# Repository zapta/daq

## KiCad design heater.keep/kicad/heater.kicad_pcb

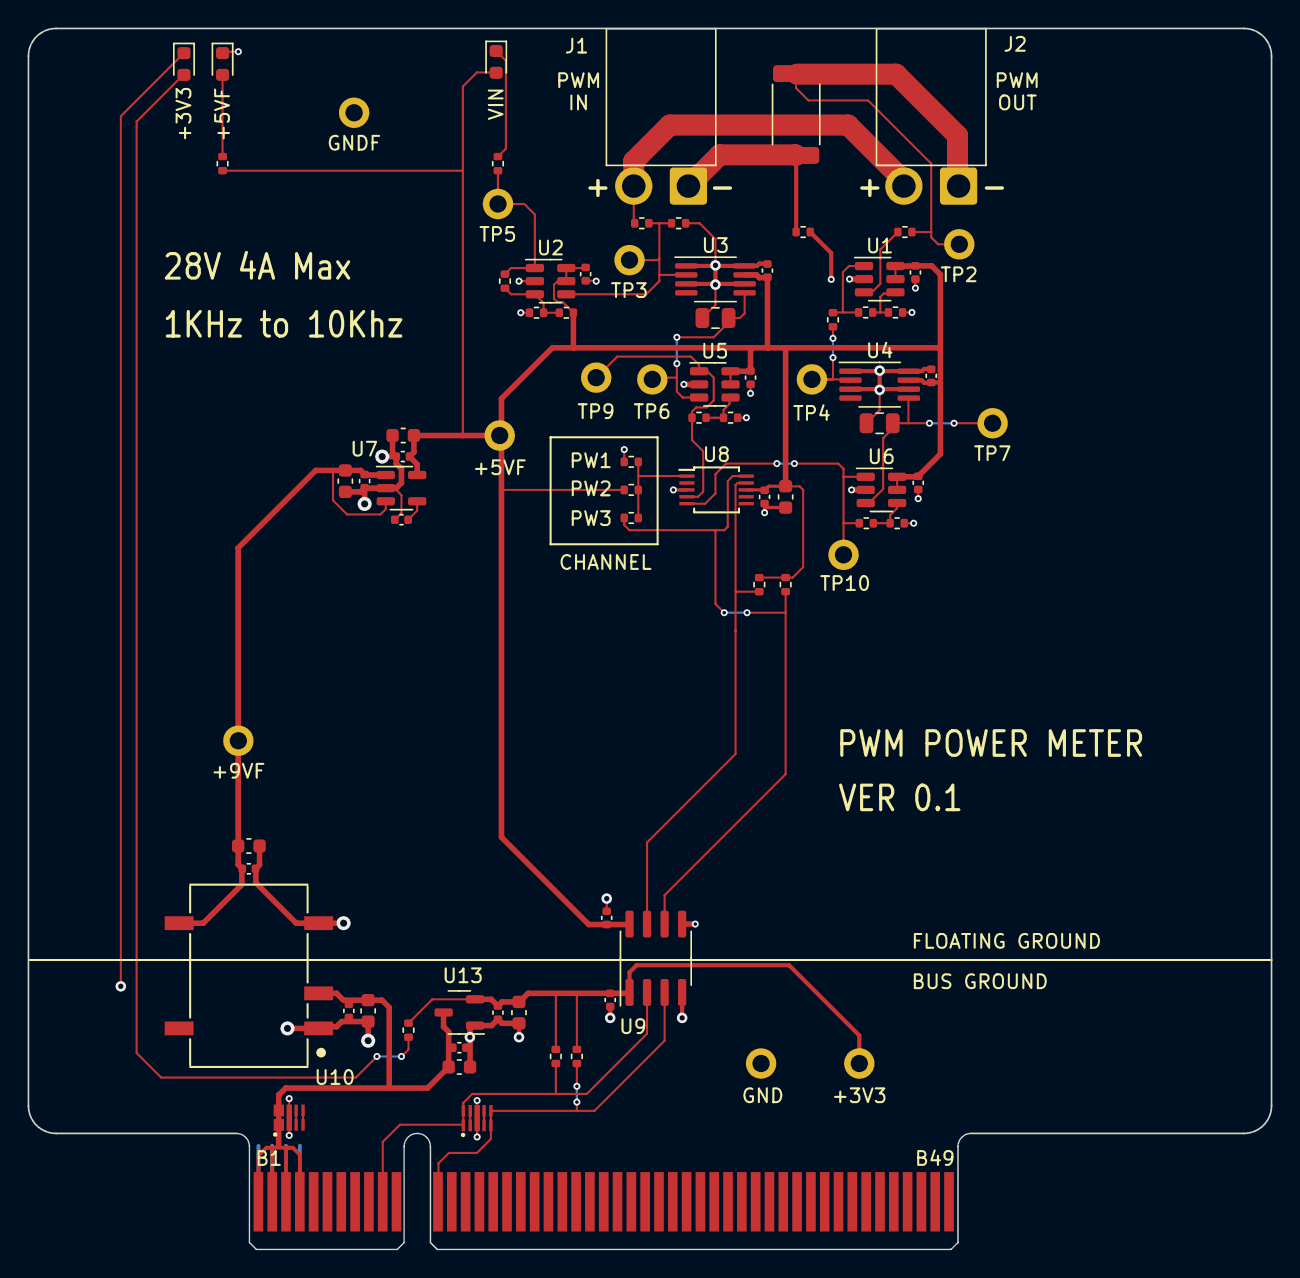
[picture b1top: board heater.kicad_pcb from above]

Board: 2 copper layers, 90.0 x 88.4 mm, 82 parts (0 on the bottom side), 31 nets.

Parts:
C1, C2, C3, C4, C7, C8, C10, C13, C18, C19, C20, C23, C24: 100n; C_0402_1005Metric
C5, C6: 2u2; C_0805_2012Metric
C9, C12, C21, C22, C25: 10u; C_0603_1608Metric
C11: 10n; C_0402_1005Metric
C14, C17: 100n 16V; C_0402_1005Metric
C15, C16: 10u 16V; C_0603_1608Metric
D1, D3: GRN; LED_0603_1608Metric
D2: RED; LED_0603_1608Metric
J1, J2: Conn_01x02_Pin; JST_VH_2_CHINESE
J3: pcie_98; PCIE_98_CARD
R1, R12, R18, R19, R20: 0R; R_0402_1005Metric
R2: 0R025 50ppm; R_2512_6332Metric
R3: 100k; R_0402_1005Metric
R4, R25: 3K3; R_0402_1005Metric
R5, R13: 5K1; R_0402_1005Metric
R6, R9, R15, R17: 10K; R_0402_1005Metric
R7: 50K; R_0402_1005Metric
R8: 2K; R_0402_1005Metric
R10: 1K; R_0402_1005Metric
R11: 1M; R_0402_1005Metric
R14, R16: 30K; R_0402_1005Metric
R21, R22, R23, R24: 1K8; R_0402_1005Metric
TP1, TP2, TP3, TP4, TP5, TP6, TP7, TP8, TP9, TP10, TP11, TP12, TP13: TestPoint; Test_Pad
U1, U2, U5, U6: OPA863SIDBVR; TSOT-23-6
U3, U4: LTC1968; MSOP-8_3x3mm_P0.65mm
U7: LP2985-5.0; SOT-23-5
U8: ADS1115IDGS; TSSOP-10_3x3mm_P0.5mm
U9: ISO1541; SOIC-8_3.9x4.9mm_P1.27mm
U10: B0509XT-1WR3; Converter_DCDC
U11, U12: ESD5344D-TP; Diodes_UDFN-10_1.0x2.5mm_P0.5mm
U13: XC6206P332MR; SOT-23-3

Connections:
+3V3: C19.2, C21.2, C23.2, R23.2, R24.2, R25.1, TP12.1, U9.1 (VCC1), U13.2 (VOUT)
+5V: C20.2, C22.2, C24.2, C25.2, J3.B1 (Pin_b1), J3.B2 (Pin_b2), J3.B3 (Pin_b3), J3.B4 (Pin_b4), U10.2 (VIN), U12.1 (D1), U12.2 (D2), U13.3 (VIN)
+5VF: C1.1, C2.1, C3.1, C4.1, C7.1, C8.1, C9.2, C10.2, C12.2, C13.1, C18.1, D2.2 (A), R5.1, R7.2, R20.2, R21.2, R22.2, TP8.1, U1.5 (~PD), U1.6 (V+), U2.5 (~PD), U2.6 (V+), U3.7 (V+), U4.7 (V+), U5.5 (~PD), U5.6 (V+), U6.5 (~PD), U6.6 (V+), U7.5 (VOUT), U8.8 (VDD), U9.8 (VCC2)
/9VF: C14.2, C15.2, C16.2, C17.2, TP11.1, U7.1 (VIN), U7.3 (ON/~OFF), U10.5 (VOUT)
/PB7: J3.B10 (Pin_b10), R23.1, U9.2 (SDA1), U11.1 (D1)
/PB8: J3.B12 (Pin_b12), R24.1, U9.3 (SCL1), U11.5 (D4)
/VIN+: J1.2, J2.2, R3.2
GND: C19.1, C20.1, C21.1, C22.1, C23.1, C24.1, C25.1, D3.1 (K), J3.A1 (Pin_a1), J3.A2 (Pin_a2), J3.A3 (Pin_a3), J3.A4 (Pin_a4), TP13.1, U9.4 (GND1), U10.1 (GND), U11.3 (GND), U12.3 (GND), U13.1 (GND)
GNDF: C1.2, C2.2, C3.2, C4.2, C5.1, C6.1, C7.2, C8.2, C9.1, C10.1, C11.1, C12.1, C13.2, C14.1, C15.1, C16.1, C17.1, C18.2, D1.1 (K), R1.2, R4.2, R8.1, R10.1, R15.1, R17.1, R19.2, TP1.1, U1.2 (V-), U2.2 (V-), U3.1 (GND), U3.3 (IN2), U3.6 (RTRN), U3.8 (EN), U4.1 (GND), U4.3 (IN2), U4.6 (RTRN), U4.8 (EN), U5.2 (V-), U6.2 (V-), U7.2 (GND), U8.3 (GND), U9.5 (GND2), U10.4 (V0)
unnamed: D1.2 (A), R5.2
unnamed: D2.1 (K), R13.2
unnamed: D3.2 (A), R25.2
unnamed: J1.1, R1.1, R2.1
unnamed: J2.1, R2.2, R6.1, TP2.1
unnamed: R11.2, R13.1, TP5.1, U2.1
unnamed: R9.1, R12.2, U1.1
unnamed: R6.2, U1.3 (+)
unnamed: R9.2, R10.2, U1.4 (-)
unnamed: R7.1, R8.2, R11.1, U2.3 (+)
unnamed: R3.1, R4.1, TP3.1, U2.4 (-), U3.2 (IN1)
unnamed: C5.2, TP6.1, U3.5 (OUT), U5.3 (+)
unnamed: R12.1, TP4.1, U4.2 (IN1)
unnamed: C6.2, TP7.1, U4.5 (OUT), U6.3 (+)
unnamed: R14.1, R15.2, U5.4 (-)
unnamed: R16.1, R17.2, U6.4 (-)
unnamed: C11.2, U7.4 (BP)
unnamed: R18.1, R19.1, R20.1, U8.1 (ADDR)
unnamed: R14.2, TP9.1, U5.1, U8.4 (AIN0)
unnamed: R16.2, TP10.1, U6.1, U8.5 (AIN1)
unnamed: R18.2, R22.1, U8.10 (SCL), U9.6 (SCL2)
unnamed: R21.1, U8.9 (SDA), U9.7 (SDA2)

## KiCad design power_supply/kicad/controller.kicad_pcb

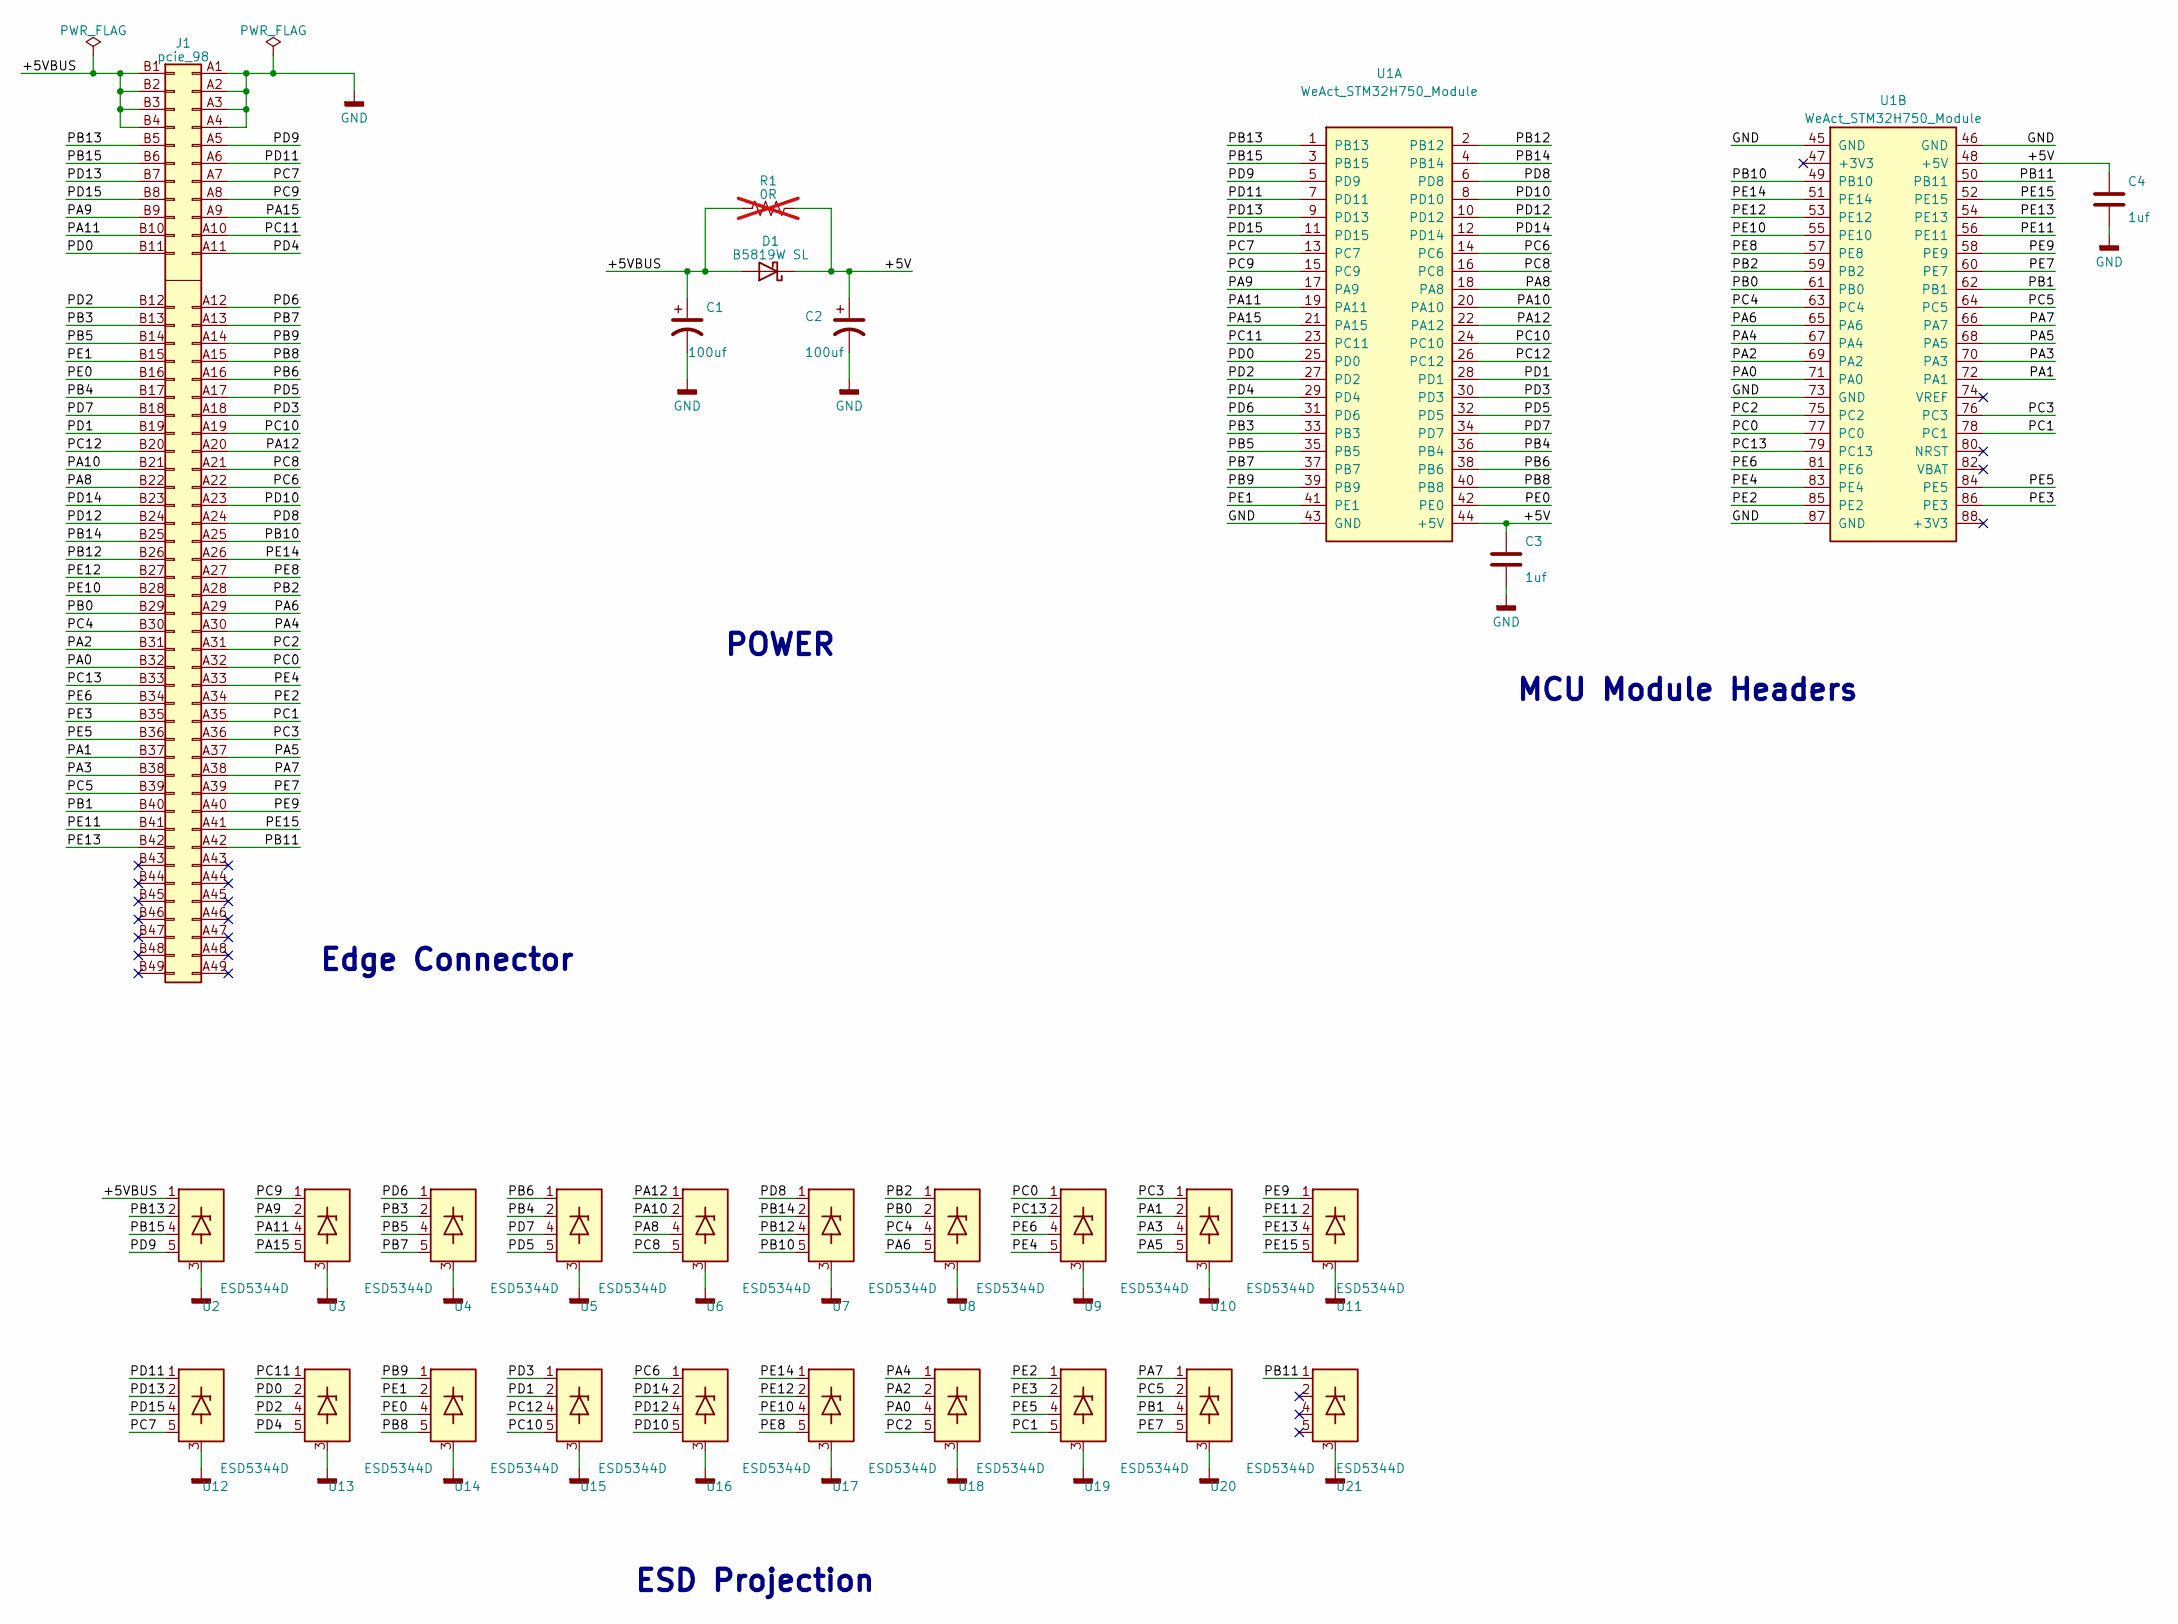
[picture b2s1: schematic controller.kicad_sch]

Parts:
C1, C2: 100uf; CP_Elec_5x5.4_JLCPCB; LCSC C131115
C3, C4: 1uf; C_0201_0603Metric; LCSC C106219
D1: B5819W SL; D_SOD-123; LCSC C8598
J1: pcie_98; pcie_98_edge; LCSC DNP
R1: 0R; R_0805_2012Metric; LCSC C17477; not fitted
U1: WeAct_STM32H750_Module; weact_stm32fh750
U2, U3, U4, U5, U6, U7, U8, U9, U10, U11, U12, U13, U14, U15, U16, U17, U18, U19, U20, U21: ESD5344D; Diodes_UDFN-10_1.0x2.5mm_P0.5mm; LCSC C2841840

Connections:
/+5V: C2.1, C3.1, C4.1, D1.1 (K), R1.2, U1.44 (+5V), U1.48 (+5V)
/+5VBUS: C1.1, D1.2 (A), J1.B1 (Pin_b1), J1.B2 (Pin_b2), J1.B3 (Pin_b3), J1.B4 (Pin_b4), R1.1, U2.1 (D1)
/PA0: J1.B32 (Pin_b32), U1.71 (PA0), U18.4 (D3)
/PA1: J1.B37 (Pin_b37), U1.72 (PA1), U10.2 (D2)
/PA2: J1.B31 (Pin_b31), U1.69 (PA2), U18.2 (D2)
/PA3: J1.B38 (Pin_b38), U1.70 (PA3), U10.4 (D3)
/PA4: J1.A30 (Pin_a30), U1.67 (PA4), U18.1 (D1)
/PA5: J1.A37 (Pin_a37), U1.68 (PA5), U10.5 (D4)
/PA6: J1.A29 (Pin_a29), U1.65 (PA6), U8.5 (D4)
/PA7: J1.A38 (Pin_a38), U1.66 (PA7), U20.1 (D1)
/PA8: J1.B22 (Pin_b22), U1.18 (PA8), U6.4 (D3)
/PA9: J1.B9 (Pin_b9), U1.17 (PA9), U3.2 (D2)
/PA10: J1.B21 (Pin_b21), U1.20 (PA10), U6.2 (D2)
/PA11: J1.B10 (Pin_b10), U1.19 (PA11), U3.4 (D3)
/PA12: J1.A20 (Pin_a20), U1.22 (PA12), U6.1 (D1)
/PA15: J1.A9 (Pin_a9), U1.21 (PA15), U3.5 (D4)
/PB0: J1.B29 (Pin_b29), U1.61 (PB0), U8.2 (D2)
/PB1: J1.B40 (Pin_b40), U1.62 (PB1), U20.4 (D3)
/PB2: J1.A28 (Pin_a28), U1.59 (PB2), U8.1 (D1)
/PB3: J1.B13 (Pin_b13), U1.33 (PB3), U4.2 (D2)
/PB4: J1.B17 (Pin_b17), U1.36 (PB4), U5.2 (D2)
/PB5: J1.B14 (Pin_b14), U1.35 (PB5), U4.4 (D3)
/PB6: J1.A16 (Pin_a16), U1.38 (PB6), U5.1 (D1)
/PB7: J1.A13 (Pin_a13), U1.37 (PB7), U4.5 (D4)
/PB8: J1.A15 (Pin_a15), U1.40 (PB8), U14.5 (D4)
/PB9: J1.A14 (Pin_a14), U1.39 (PB9), U14.1 (D1)
/PB10: J1.A25 (Pin_a25), U1.49 (PB10), U7.5 (D4)
/PB11: J1.A42 (Pin_a42), U1.50 (PB11), U21.1 (D1)
/PB12: J1.B26 (Pin_b26), U1.2 (PB12), U7.4 (D3)
/PB13: J1.B5 (Pin_b5), U1.1 (PB13), U2.2 (D2)
/PB14: J1.B25 (Pin_b25), U1.4 (PB14), U7.2 (D2)
/PB15: J1.B6 (Pin_b6), U1.3 (PB15), U2.4 (D3)
/PC0: J1.A32 (Pin_a32), U1.77 (PC0), U9.1 (D1)
/PC1: J1.A35 (Pin_a35), U1.78 (PC1), U19.5 (D4)
/PC2: J1.A31 (Pin_a31), U1.75 (PC2), U18.5 (D4)
/PC3: J1.A36 (Pin_a36), U1.76 (PC3), U10.1 (D1)
/PC4: J1.B30 (Pin_b30), U1.63 (PC4), U8.4 (D3)
/PC5: J1.B39 (Pin_b39), U1.64 (PC5), U20.2 (D2)
/PC6: J1.A22 (Pin_a22), U1.14 (PC6), U16.1 (D1)
/PC7: J1.A7 (Pin_a7), U1.13 (PC7), U12.5 (D4)
/PC8: J1.A21 (Pin_a21), U1.16 (PC8), U6.5 (D4)
/PC9: J1.A8 (Pin_a8), U1.15 (PC9), U3.1 (D1)
/PC10: J1.A19 (Pin_a19), U1.24 (PC10), U15.5 (D4)
/PC11: J1.A10 (Pin_a10), U1.23 (PC11), U13.1 (D1)
/PC12: J1.B20 (Pin_b20), U1.26 (PC12), U15.4 (D3)
/PC13: J1.B33 (Pin_b33), U1.79 (PC13), U9.2 (D2)
/PD0: J1.B11 (Pin_b11), U1.25 (PD0), U13.2 (D2)
/PD1: J1.B19 (Pin_b19), U1.28 (PD1), U15.2 (D2)
/PD2: J1.B12 (Pin_b12), U1.27 (PD2), U13.4 (D3)
/PD3: J1.A18 (Pin_a18), U1.30 (PD3), U15.1 (D1)
/PD4: J1.A11, U1.29 (PD4), U13.5 (D4)
/PD5: J1.A17 (Pin_a17), U1.32 (PD5), U5.5 (D4)
/PD6: J1.A12 (Pin_a12), U1.31 (PD6), U4.1 (D1)
/PD7: J1.B18 (Pin_b18), U1.34 (PD7), U5.4 (D3)
/PD8: J1.A24 (Pin_a24), U1.6 (PD8), U7.1 (D1)
/PD9: J1.A5 (Pin_a5), U1.5 (PD9), U2.5 (D4)
/PD10: J1.A23 (Pin_a23), U1.8 (PD10), U16.5 (D4)
/PD11: J1.A6 (Pin_a6), U1.7 (PD11), U12.1 (D1)
/PD12: J1.B24 (Pin_b24), U1.10 (PD12), U16.4 (D3)
/PD13: J1.B7 (Pin_b7), U1.9 (PD13), U12.2 (D2)
/PD14: J1.B23 (Pin_b23), U1.12 (PD14), U16.2 (D2)
/PD15: J1.B8 (Pin_b8), U1.11 (PD15), U12.4 (D3)
/PE0: J1.B16 (Pin_b16), U1.42 (PE0), U14.4 (D3)
/PE1: J1.B15 (Pin_b15), U1.41 (PE1), U14.2 (D2)
/PE2: J1.A34 (Pin_a34), U1.85 (PE2), U19.1 (D1)
/PE3: J1.B35 (Pin_b35), U1.86 (PE3), U19.2 (D2)
/PE4: J1.A33 (Pin_a33), U1.83 (PE4), U9.5 (D4)
/PE5: J1.B36 (Pin_b36), U1.84 (PE5), U19.4 (D3)
/PE6: J1.B34 (Pin_b34), U1.81 (PE6), U9.4 (D3)
/PE7: J1.A39 (Pin_a39), U1.60 (PE7), U20.5 (D4)
/PE8: J1.A27 (Pin_a27), U1.57 (PE8), U17.5 (D4)
/PE9: J1.A40 (Pin_a40), U1.58 (PE9), U11.1 (D1)
/PE10: J1.B28 (Pin_b28), U1.55 (PE10), U17.4 (D3)
/PE11: J1.B41 (Pin_b41), U1.56 (PE11), U11.2 (D2)
/PE12: J1.B27 (Pin_b27), U1.53 (PE12), U17.2 (D2)
/PE13: J1.B42 (Pin_b42), U1.54 (PE13), U11.4 (D3)
/PE14: J1.A26 (Pin_a26), U1.51 (PE14), U17.1 (D1)
/PE15: J1.A41 (Pin_a41), U1.52 (PE15), U11.5 (D4)
GND: C1.2, C2.2, C3.2, C4.2, J1.A1 (Pin_a1), J1.A2 (Pin_a2), J1.A3 (Pin_a3), J1.A4 (Pin_a4), U1.43 (GND), U1.45 (GND), U1.46 (GND), U1.73 (GND), U1.87 (GND), U2.3 (GND), U3.3 (GND), U4.3 (GND), U5.3 (GND), U6.3 (GND), U7.3 (GND), U8.3 (GND), U9.3 (GND), U10.3 (GND), U11.3 (GND), U12.3 (GND), U13.3 (GND), U14.3 (GND), U15.3 (GND), U16.3 (GND), U17.3 (GND), U18.3 (GND), U19.3 (GND), U20.3 (GND), U21.3 (GND)

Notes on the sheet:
ESD Projection
MCU Module Headers
Edge Connector
POWER

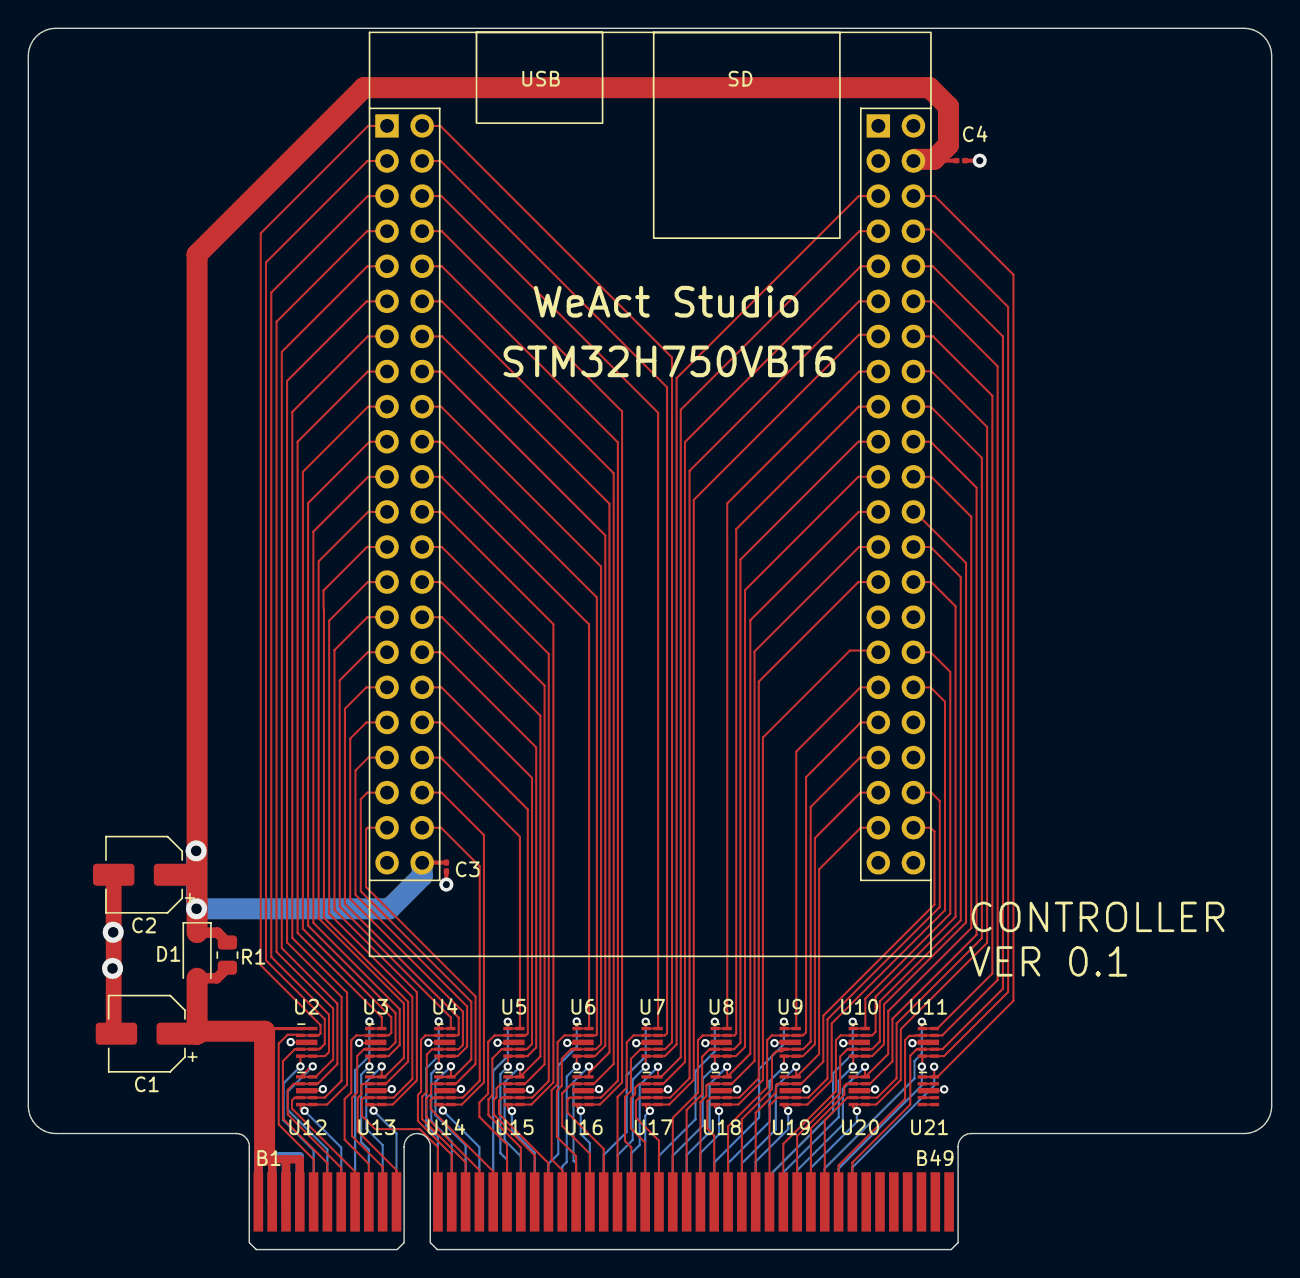
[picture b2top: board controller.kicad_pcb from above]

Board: 2 copper layers, 90.0 x 88.4 mm, 28 parts (0 on the bottom side), 79 nets.
